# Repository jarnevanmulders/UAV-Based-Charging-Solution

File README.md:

# UAV Based Charging Solution

- [NRF52832 DK pinout](https://os.mbed.com/platforms/Nordic-nRF52-DK/)
- [NRF52832 DK schematics](https://devzone.nordicsemi.com/cfs-file/__key/communityserver-discussions-components-files/4/PCA10040_5F00_Schematic_5F00_And_5F00_PCB.pdf)

# HW design
- [BLE 2.4GHz antenna design](https://www.infineon.com/dgdl/Infineon-AN91445_Antenna_Design_and_RF_Layout_Guidelines-ApplicationNotes-v09_00-EN.pdf)

# Image hardware

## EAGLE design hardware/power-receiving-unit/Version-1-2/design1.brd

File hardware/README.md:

# Hardware status
## PRU
Working

Updates from v1.0 to v1.1
- I2C programmable load
- VDD_BLE directly connected to ADC pin P03 (without voltage divider)
- Additional RC filter after current limiter OPAMP
- Button from pull-up to pull down
- Additional filter (ferrite bead) on VDD_BLE supply line
- Other load switch implementation (with dual PMOS PMDPB55XP)
- Diode and shunt resistor location changed
- MIFA antenna tuning
  - Measured impedance 25+j25
    - Measured with R&S ZVL 3GHz VNA
    - Used a calibrated UFL connector cable (calibrated with ZVL one port calibration procedure)
    - Blank PCB board was used for measurement
  - Added 1.2 pF parallel with antenna (as compensation (see Smith V4.1))
  - Total [Pi] matching circuit (MCU - 0.8 pF capacitor - 3.9 nH inductor - 1.2 pF capacitor)

## PTU

### Architecture

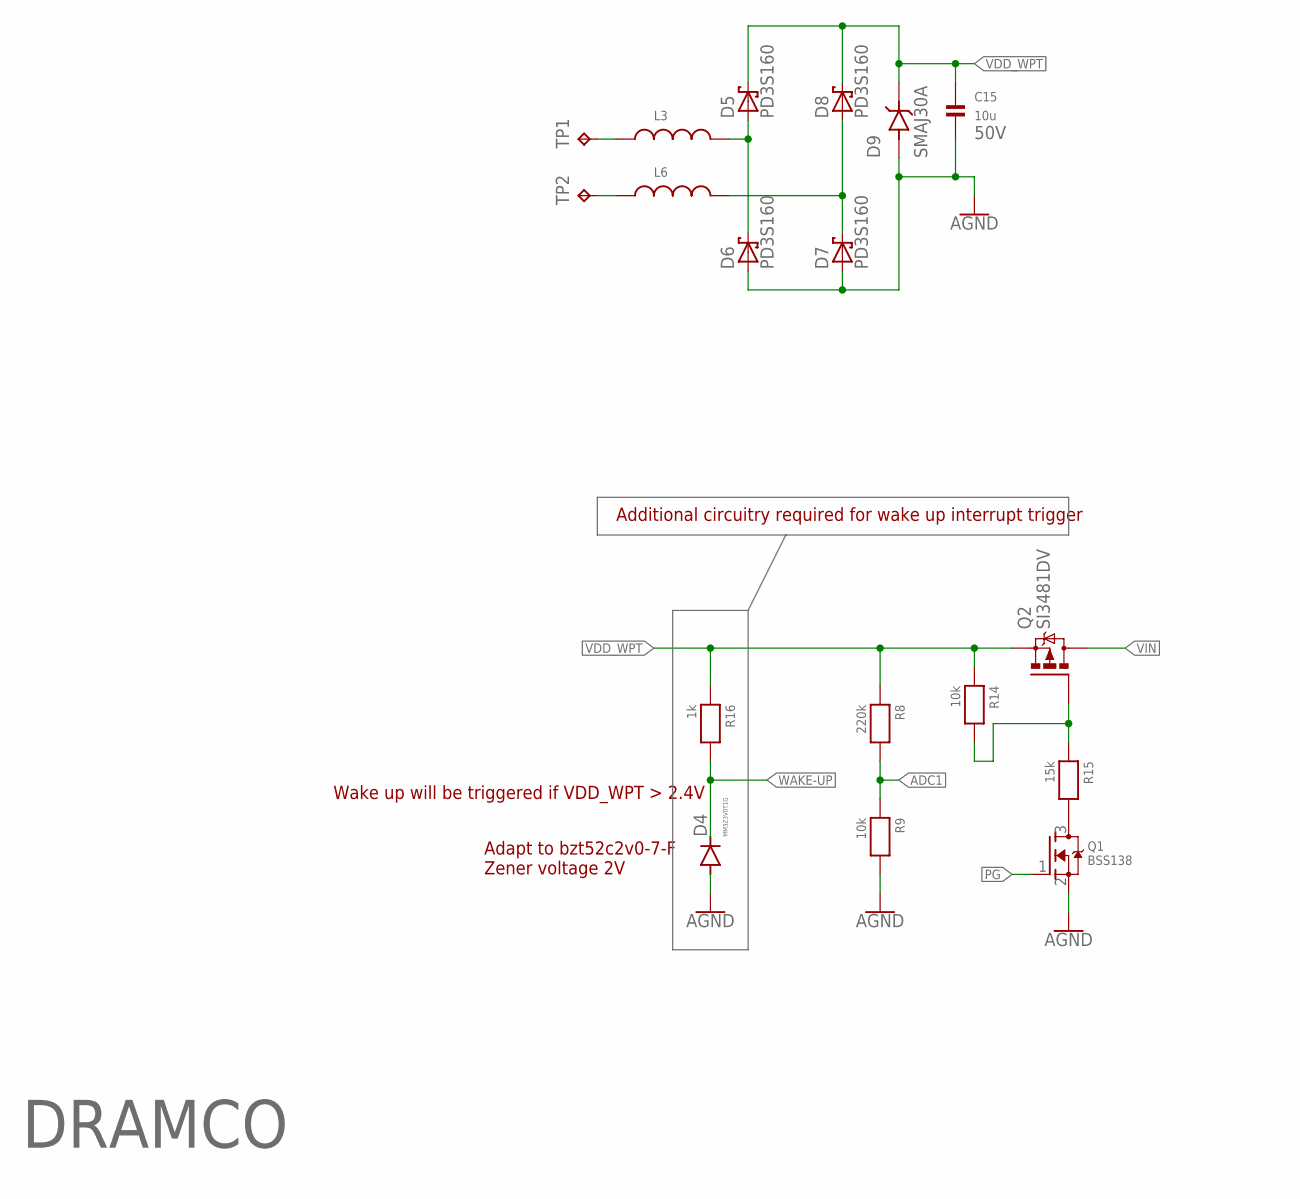
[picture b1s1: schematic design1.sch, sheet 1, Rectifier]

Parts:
C15: 10u; 1206
D4: MM3Z3V0T1G; SOD323-R
D5, D6, D7, D8: PD3S160; POWERDI323
D9: SMAJ30A; DIOM5026X229N
L3, L6: WE-CAIR_4248_744912182; WE-CAIR_4248
Q1: BSS138; SOT23-R
Q2: SI3481DV; TSOP-6.PAC
R8: 220k; 0603
R9, R14: 10k; 0603
R15: 15k; 0603
R16: 1k; 0603
TP1, TP2: TPTP20SQ; TP20SQ

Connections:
ADC1: R8.2, R9.1; also elsewhere on the board
AGND: C15.2, D4.A, D6.A, D7.A, D9.A, Q1.2 (S), R9.2; also elsewhere on the board
unnamed: Q1.3 (D), R15.2
unnamed: Q2.3 (G), R14.2, R15.1
unnamed: L6.1, TP2.TP
unnamed: L3.1, TP1.TP
unnamed: D5.A, D6.C, L3.2
unnamed: D7.C, D8.A, L6.2
PG: Q1.1 (G); also elsewhere on the board
VDD_WPT: C15.1, D5.C, D8.C, D9.C, Q2.4 (S), R8.1, R14.1, R16.1
VIN: Q2.1 (D), Q2.2 (D), Q2.5 (D), Q2.6 (D); also elsewhere on the board
WAKE-UP: D4.C, R16.2; also elsewhere on the board

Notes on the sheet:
Additional circuitry required for wake up interrupt trigger
50V
DRAMCO
Adapt to bzt52c2v0-7-F Zener voltage 2V
Wake up will be triggered if VDD_WPT > 2.4V

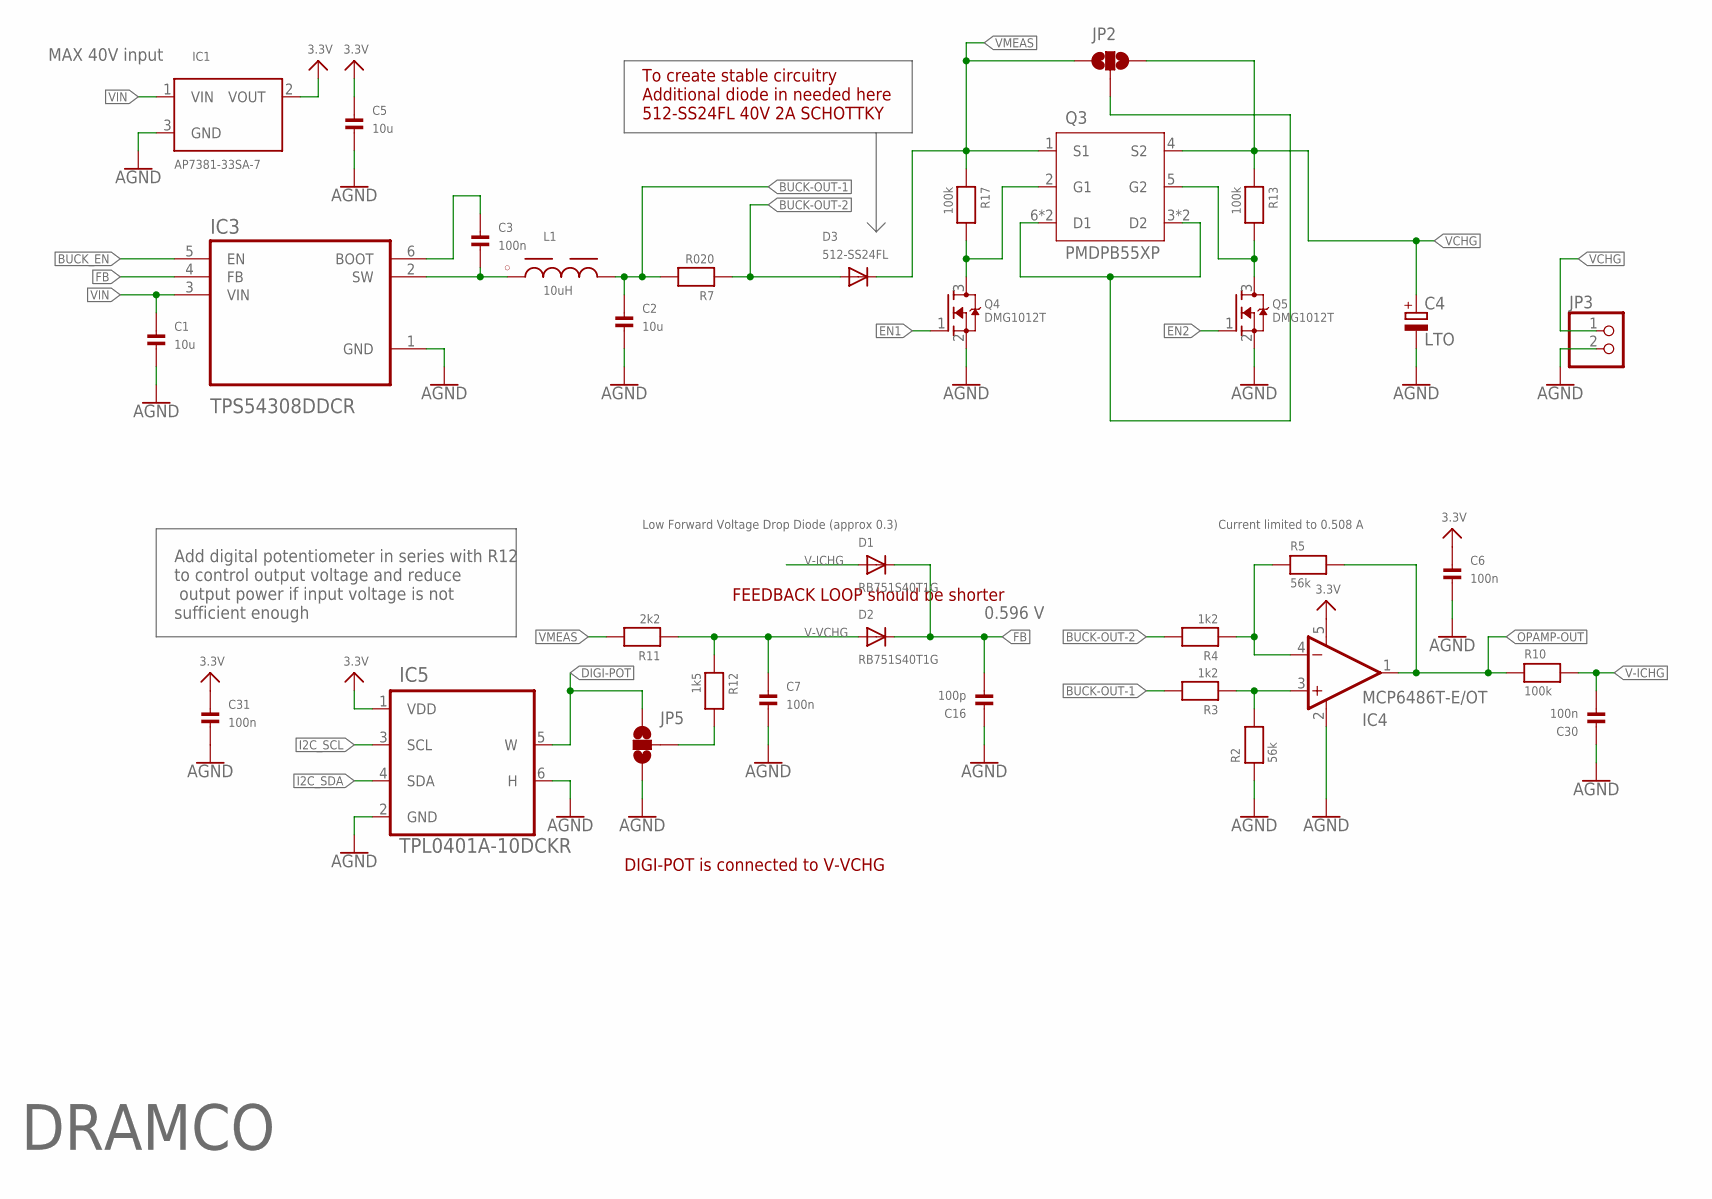
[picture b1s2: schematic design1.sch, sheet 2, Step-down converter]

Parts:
C1, C2, C5: 10u; 0603
C3, C7, C30: 100n; 0603
C4: LTO; E5-10,5
C6, C31: 100n; 0402
C16: 100p; 0603
D1, D2: RB751S40T1G; SOD-523
D3: 512-SS24FL; SOD-123
IC1: AP7381-33SA-7; SOT23-R
IC3: TPS54308DDCR; SOT95P280X110-6N
IC4: MCP6486T-E/OT; SOT23-5
IC5: TPL0401A-10DCKR; SOT65P210X110-6N
JP2, JP5: JUMPER-SMT_3_NO_NO-SILK; SMT-JUMPER_3_NO_NO-SILK
JP3: HEADER-1X2ROUND; 1X02_ROUND
L1: 10uH; WE-PD_7332/7345_PLASTIC_BASE
Q3: PMDPB55XP; SON65P200X200X65-8N
Q4, Q5: DMG1012T; SOT523-3
R2, R5: 56k; 0603
R3, R4: 1k2; 0603
R7: R020; 0603
R10: 100k; 0603
R11: 2k2; 0603
R12: 1k5; 0603
R13, R17: 100k; 0402

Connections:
3.3V: C5.1, C6.1, C31.1, IC1.2 (VOUT), IC4.5 (V+), IC5.1 (VDD)
AGND: C1.2, C2.2, C4.-, C5.2, C6.2, C7.2, C16.1, C30.1, C31.2, IC1.3 (GND), IC3.1 (GND), IC4.2 (V-), IC5.2 (GND), IC5.6 (H), JP3.2, JP5.1, Q4.2 (S), Q5.2 (S), R2.1; also elsewhere on the board
BUCK-OUT-1: C2.1, L1.2, R3.2, R7.2
BUCK-OUT-2: D3.A, R4.2, R7.1
BUCK_EN: IC3.5 (EN); also elsewhere on the board
DIGI-POT: IC5.5 (W), JP5.3
EN1: Q4.1 (G); also elsewhere on the board
EN2: Q5.1 (G); also elsewhere on the board
FB: C16.2, D1.K (C), D2.K (C), IC3.4 (FB)
I2C_SCL: IC5.3 (SCL); also elsewhere on the board
I2C_SDA: IC5.4 (SDA); also elsewhere on the board
unnamed: JP2.2, Q3.3 (D2), Q3.6 (D1), Q3.7 (D1), Q3.8 (D2)
unnamed: C3.1, IC3.6 (BOOT)
unnamed: C3.2, IC3.2 (SW), L1.1
unnamed: JP5.2, R12.2
unnamed: IC4.4 (-IN), R4.1, R5.1
unnamed: IC4.3 (+IN), R2.2, R3.1
unnamed: Q3.2 (G1), Q4.3 (D), R17.2
unnamed: Q3.5 (G2), Q5.3 (D), R13.2
OPAMP-OUT: IC4.1 (OUT), R5.2, R10.1
V-ICHG: C30.2, D1.A, R10.2; also elsewhere on the board
V-VCHG: C7.1, D2.A, R11.1, R12.1
VCHG: C4.+, JP2.3, JP3.1, Q3.4 (S2), R13.1; also elsewhere on the board
VIN: C1.1, IC1.1 (VIN), IC3.3 (VIN); also elsewhere on the board
VMEAS: D3.C, JP2.1, Q3.1 (S1), R11.2, R17.1

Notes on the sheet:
Low Forward Voltage Drop Diode (approx 0.3)
0.596 V
To create stable circuitry Additional diode in needed here 512-SS24FL 40V 2A SCHOTTKY
Add digital potentiometer in series with R12 to control output voltage and reduce output power if input voltage is not sufficient enough
DRAMCO
Current limited to 0.508 A
MAX 40V input
DIGI-POT is connected to V-VCHG
FEEDBACK LOOP should be shorter

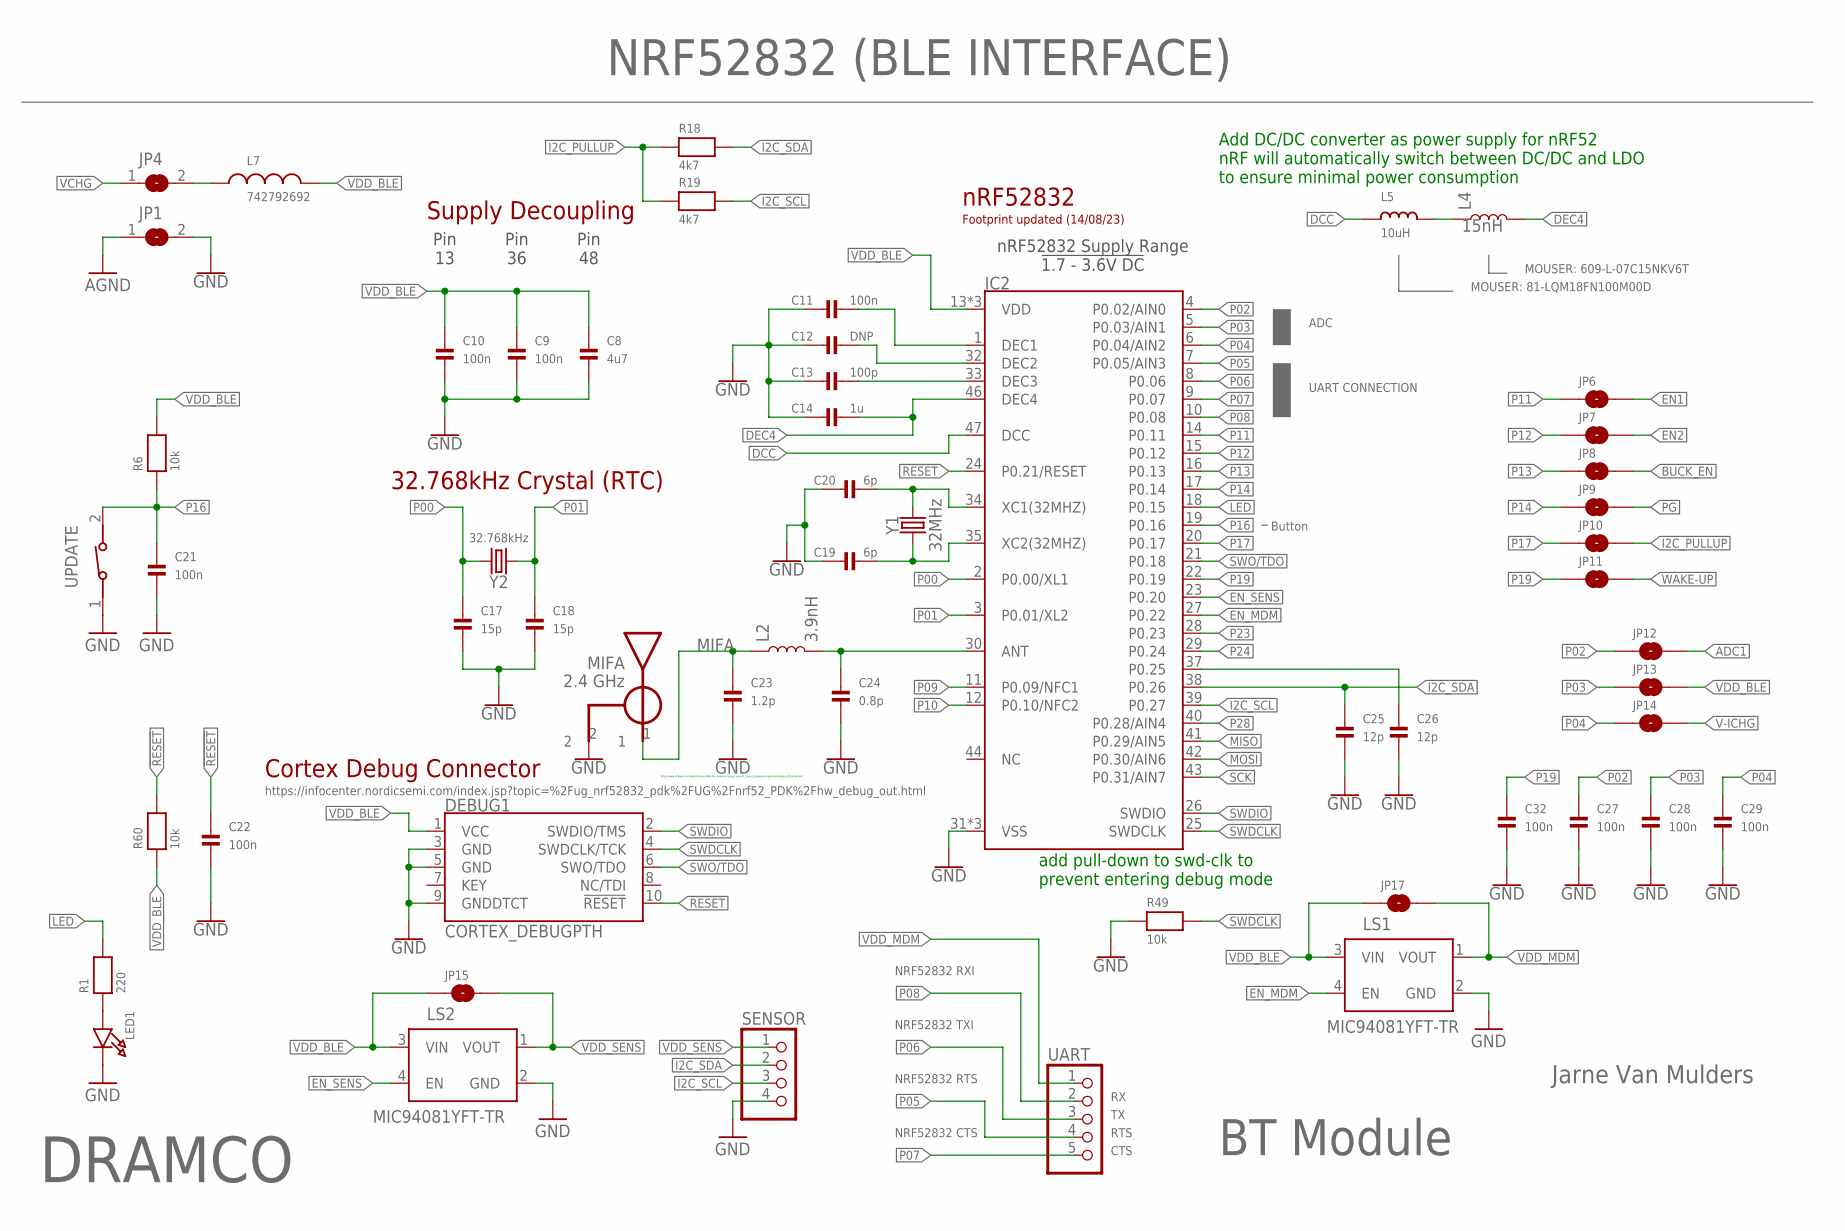
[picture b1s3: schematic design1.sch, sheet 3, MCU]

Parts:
C8: 4u7; 0603
C9, C10, C11, C21, C22, C27, C28, C29, C32: 100n; 0402
C12: DNP; 0402
C13: 100p; 0402
C14: 1u; 0402
C17, C18: 15p; 0402
C19, C20: 6p; 0402
C23: 1.2p; 0402
C24: 0.8p; 0402
C25, C26: 12p; 0402
DEBUG1: CORTEX_DEBUGPTH; 2X5-PTH-1.27MM
IC2: NRF52832-EXTENDED; QFN48-6X6MM-EXTENDED
JP1, JP4: SOLDERJUMPERREFLOW_NOPASTE; SOLDERJUMPER_REFLOW_NOPASTE
JP6, JP7, JP8, JP9, JP10, JP11, JP12, JP13, JP14, JP15, JP17: JUMPER-SMT_2_NO_NO-SILK; SMT-JUMPER_2_NO_NO-SILK
L2: 3.9nH; 0402
L4: 15nH; 0402
L5: 10uH; _0603MP
L7: 742792692; WE-CBF_0603(W=2.2)
LED1: LED0805; CHIPLED_0805
LS1, LS2: MIC94081YFT-TR; IC_MIC94081YFT-TR
R1: 220; 0603
R6, R49, R60: 10k; 0402
R18, R19: 4k7; 0402
SENSOR: HEADER-1X4ROUND; 1X04_ROUND
U$18: BLE-ANT; ANT-2G4
UART: HEADER-1X5ROUND; 1X05_ROUND
UPDATE: 434111043826
Y1: 32MHz; CRYSTAL-SMD-2.0X1.6MM
Y2: 32.768kHz; CRYSTAL-SMD-3.2X1.5MM

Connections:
!RESET!: C22.1, DEBUG1.10 (!RESET), IC2.24 (P0.21/RESET), R60.2
ADC1: JP12.2; also elsewhere on the board
AGND: JP1.1; also elsewhere on the board
ANT: C24.1, IC2.30 (ANT), L2.2
BUCK_EN: JP8.2; also elsewhere on the board
DCC: IC2.47 (DCC), L5.1
DEC4: C14.2, IC2.46 (DEC4), L4.2
DEC5: C11.2, IC2.1 (DEC1)
DEC6: C12.2, IC2.32 (DEC2)
DEC8: C13.2, IC2.33 (DEC3)
EN1: JP6.2; also elsewhere on the board
EN2: JP7.2; also elsewhere on the board
EN_MDM: IC2.27 (P0.22), LS1.4 (EN)
EN_SENS: IC2.23 (P0.20), LS2.4 (EN)
GND: C8.2, C9.2, C10.2, C11.1, C12.1, C13.1, C14.1, C17.2, C18.2, C19.1, C20.1, C21.2, C22.2, C23.2, C24.2, C25.2, C26.2, C27.2, C28.2, C29.2, C32.2, DEBUG1.3 (GND), DEBUG1.5 (GND), DEBUG1.9 (GNDDTCT), IC2.31 (VSS), IC2.45 (VSS), IC2.EP (VSS), JP1.2, LED1.C, LS1.2 (GND), LS2.2 (GND), R49.1, SENSOR.4, U$18.2, UPDATE.1
I2C_PULLUP: JP10.2, R18.1, R19.1
I2C_SCL: IC2.39 (P0.27), R19.2, SENSOR.3; also elsewhere on the board
I2C_SDA: C25.1, IC2.38 (P0.26), R18.2, SENSOR.2; also elsewhere on the board
LED: IC2.18 (P0.15), R1.2
MIFA: C23.1, L2.1, U$18.1
MISO: IC2.41 (P0.29/AIN5)
MOSI: IC2.42 (P0.30/AIN6)
unnamed: JP4.2, L7.1
unnamed: LED1.A, R1.1
unnamed: C26.1, IC2.37 (P0.25)
unnamed: L4.1, L5.2
P00: C17.1, IC2.2 (P0.00/XL1), Y2.P$2 (2)
P01: C18.1, IC2.3 (P0.01/XL2), Y2.P$1 (1)
P02: C27.1, IC2.4 (P0.02/AIN0), JP12.1
P03: C28.1, IC2.5 (P0.03/AIN1), JP13.1
P04: C29.1, IC2.6 (P0.04/AIN2), JP14.1
P05: IC2.7 (P0.05/AIN3), UART.4
P06: IC2.8 (P0.06), UART.3
P07: IC2.9 (P0.07), UART.5
P08: IC2.10 (P0.08), UART.2
P09: IC2.11 (P0.09/NFC1)
P10: IC2.12 (P0.10/NFC2)
P11: IC2.14 (P0.11), JP6.1
P12: IC2.15 (P0.12), JP7.1
P13: IC2.16 (P0.13), JP8.1
P14: IC2.17 (P0.14), JP9.1
P16: C21.1, IC2.19 (P0.16), R6.1, UPDATE.2
P17: IC2.20 (P0.17), JP10.1
P19: C32.1, IC2.22 (P0.19), JP11.1
P23: IC2.28 (P0.23)
P24: IC2.29 (P0.24)
P28: IC2.40 (P0.28/AIN4)
PG: JP9.2; also elsewhere on the board
SCK: IC2.43 (P0.31/AIN7)
SWDCLK: DEBUG1.4 (SWDCLK/TCK), IC2.25 (SWDCLK), R49.2
SWDIO: DEBUG1.2 (SWDIO/TMS), IC2.26 (SWDIO)
SWO/TDO: DEBUG1.6 (SWO/TDO), IC2.21 (P0.18)
V-ICHG: JP14.2; also elsewhere on the board
VCHG: JP4.1; also elsewhere on the board
VDD_BLE: C8.1, C9.1, C10.1, DEBUG1.1 (VCC), IC2.13 (VDD), IC2.36 (VDD), IC2.48 (VDD), JP13.2, JP15.1, JP17.1, L7.2, LS1.3 (VIN), LS2.3 (VIN), R6.2, R60.1
VDD_MDM: JP17.2, LS1.1 (VOUT), UART.1
VDD_SENS: JP15.2, LS2.1 (VOUT), SENSOR.1
WAKE-UP: JP11.2; also elsewhere on the board
XC1: C20.2, IC2.34 (XC1(32MHZ)), Y1.3 (2)
XC2: C19.2, IC2.35 (XC2(32MHZ)), Y1.1

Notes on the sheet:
BT Module
Jarne Van Mulders
DRAMCO
NRF52832 (BLE INTERFACE)
Pin 13
Pin 36
Pin 48
nRF52832
32.768kHz Crystal (RTC)
Supply Decoupling
Cortex Debug Connector
nRF52832 Supply Range !1.7 - 3.6V DC!
Add DC/DC converter as power supply for nRF52 nRF will automatically switch between DC/DC and LDO to ensure minimal power consumption
add pull-down to swd-clk to prevent entering debug mode
NRF52832 RXI
NRF52832 TXI
NRF52832 RTS
NRF52832 CTS
MOUSER: 81-LQM18FN100M00D
MOUSER: 609-L-07C15NKV6T
RTS
CTS
UART CONNECTION
Button
ADC
https://www.infineon.com/dgdl/Infineon-AN91445_Antenna_Design_and_RF_Layout_Guidelines-ApplicationNotes-v09_00-EN.pdf
https://infocenter.nordicsemi.com/index.jsp?topic=%2Fug_nrf52832_pdk%2FUG%2Fnrf52_PDK%2Fhw_debug_out.html
Footprint updated (14/08/23)

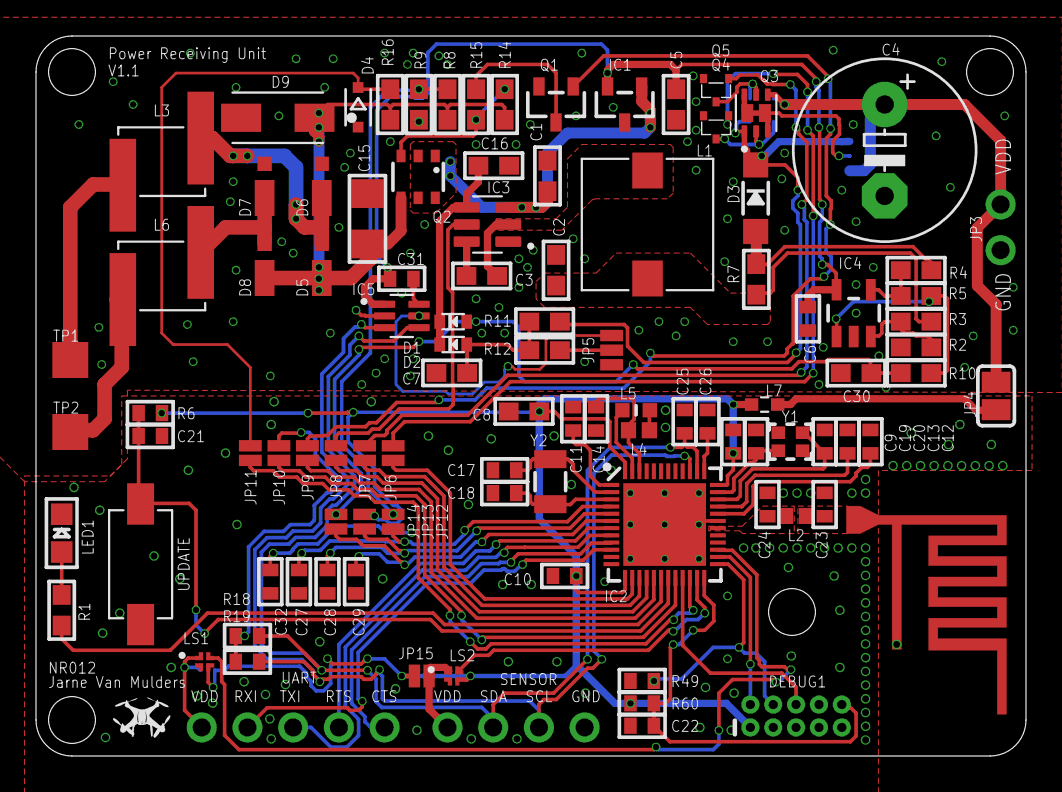
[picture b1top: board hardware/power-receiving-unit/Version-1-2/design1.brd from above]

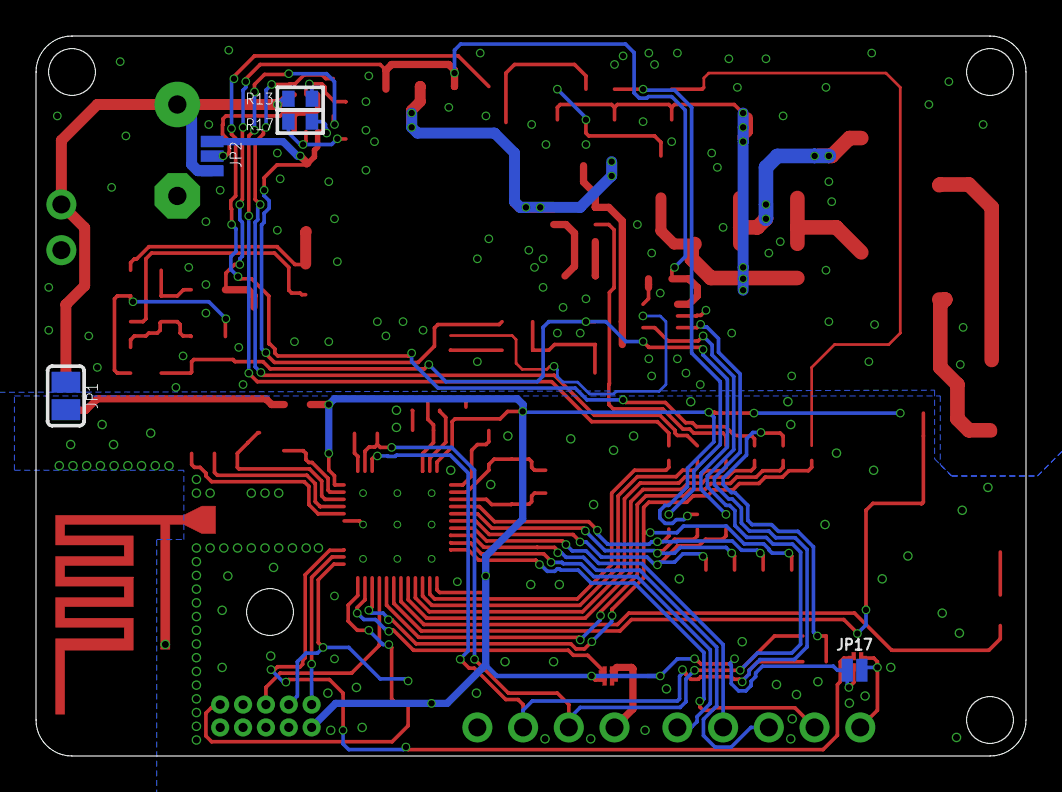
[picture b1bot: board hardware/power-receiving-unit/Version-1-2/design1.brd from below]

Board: 2 copper layers, 55.0 x 40.0 mm, 107 parts (5 on the bottom side), 76 nets.

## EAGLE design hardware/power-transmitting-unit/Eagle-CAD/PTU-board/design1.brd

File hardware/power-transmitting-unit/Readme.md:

## Hardware status

## Architecture

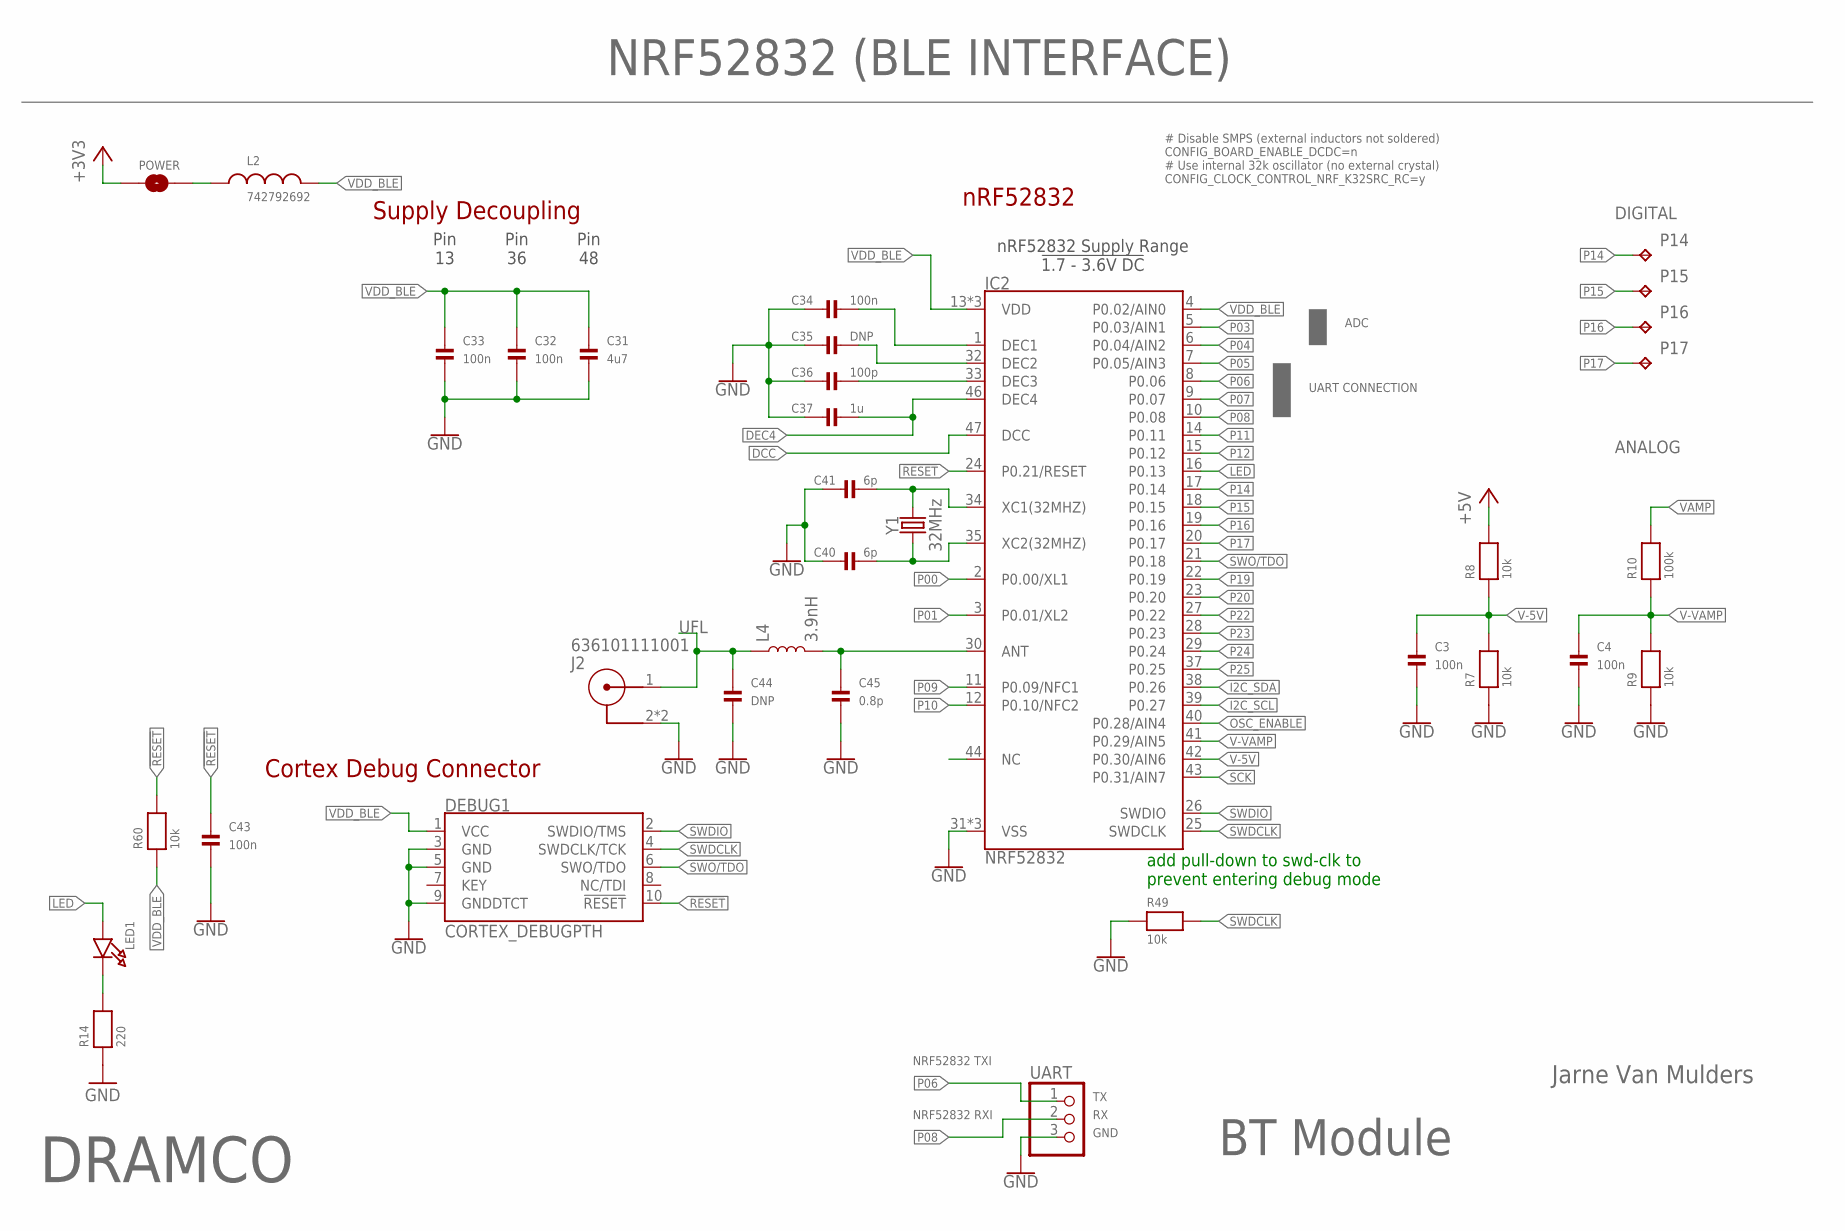
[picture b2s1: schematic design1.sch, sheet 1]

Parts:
C3, C4, C32, C33, C34, C43: 100n; 0402
C31: 4u7; 0603
C35, C44: DNP; 0402
C36: 100p; 0402
C37: 1u; 0402
C40, C41: 6p; 0402
C45: 0.8p; 0402
DEBUG1: CORTEX_DEBUGPTH; 2X5-PTH-1.27MM
IC2: NRF52832; QFN48-6X6MM-EXTENDED
J2: 636101111001
L2: 742792692; WE-CBF_0603(W=2.2)
L4: 3.9nH; 0402
LED1: LED0805; CHIPLED_0805
P14, P15, P16, P17: TPTP10SQ; TP10SQ
POWER: JUMPER-SMT_2_NO_NO-SILK; SMT-JUMPER_2_NO_NO-SILK
R7, R8, R9, R49, R60: 10k; 0402
R10: 100k; 0402
R14: 220; 0603
UART: HEADER-1X3ROUND; 1X03_ROUND
Y1: 32MHz; CRYSTAL-SMD-2.0X1.6MM

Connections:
!RESET!: C43.1, DEBUG1.10 (!RESET), IC2.24 (P0.21/RESET), R60.2
+3V3: POWER.1; also elsewhere on the board
+5V: R8.2; also elsewhere on the board
ANT: C45.1, IC2.30 (ANT), L4.2
DCC: IC2.47 (DCC)
DEC4: C37.2, IC2.46 (DEC4)
DEC5: C34.2, IC2.1 (DEC1)
DEC6: C35.2, IC2.32 (DEC2)
DEC8: C36.2, IC2.33 (DEC3)
GND: C3.2, C4.2, C31.2, C32.2, C33.2, C34.1, C35.1, C36.1, C37.1, C40.1, C41.1, C43.2, C44.2, C45.2, DEBUG1.3 (GND), DEBUG1.5 (GND), DEBUG1.9 (GNDDTCT), IC2.31 (VSS), IC2.45 (VSS), IC2.EP (VSS), J2.2, J2.3 (2), R7.1, R9.1, R14.1, R49.1, UART.3; also elsewhere on the board
I2C_SCL: IC2.39 (P0.27); also elsewhere on the board
I2C_SDA: IC2.38 (P0.26); also elsewhere on the board
LED: IC2.16 (P0.13), LED1.A
unnamed: LED1.C, R14.2
unnamed: L2.1, POWER.2
NC: IC2.44 (NC)
OSC_ENABLE: IC2.40 (P0.28/AIN4); also elsewhere on the board
P00: IC2.2 (P0.00/XL1)
P01: IC2.3 (P0.01/XL2)
P03: IC2.5 (P0.03/AIN1)
P04: IC2.6 (P0.04/AIN2)
P05: IC2.7 (P0.05/AIN3)
P06: IC2.8 (P0.06), UART.1
P07: IC2.9 (P0.07)
P08: IC2.10 (P0.08), UART.2
P09: IC2.11 (P0.09/NFC1)
P10: IC2.12 (P0.10/NFC2)
P11: IC2.14 (P0.11)
P12: IC2.15 (P0.12)
P14: IC2.17 (P0.14), P14.TP
P15: IC2.18 (P0.15), P15.TP
P16: IC2.19 (P0.16), P16.TP
P17: IC2.20 (P0.17), P17.TP
P19: IC2.22 (P0.19)
P20: IC2.23 (P0.20)
P22: IC2.27 (P0.22)
P23: IC2.28 (P0.23)
P24: IC2.29 (P0.24)
P25: IC2.37 (P0.25)
SCK: IC2.43 (P0.31/AIN7)
SWDCLK: DEBUG1.4 (SWDCLK/TCK), IC2.25 (SWDCLK), R49.2
SWDIO: DEBUG1.2 (SWDIO/TMS), IC2.26 (SWDIO)
SWO/TDO: DEBUG1.6 (SWO/TDO), IC2.21 (P0.18)
UFL: C44.1, J2.1, L4.1
V-5V: C3.1, IC2.42 (P0.30/AIN6), R7.2, R8.1
V-VAMP: C4.1, IC2.41 (P0.29/AIN5), R9.2, R10.1
VAMP: R10.2; also elsewhere on the board
VDD_BLE: C31.1, C32.1, C33.1, DEBUG1.1 (VCC), IC2.4 (P0.02/AIN0), IC2.13 (VDD), IC2.36 (VDD), IC2.48 (VDD), L2.2, R60.1
XC1: C41.2, IC2.34 (XC1(32MHZ)), Y1.3 (2)
XC2: C40.2, IC2.35 (XC2(32MHZ)), Y1.1

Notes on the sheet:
BT Module
Jarne Van Mulders
DRAMCO
NRF52832 (BLE INTERFACE)
Pin 13
Pin 36
Pin 48
nRF52832
Supply Decoupling
Cortex Debug Connector
nRF52832 Supply Range !1.7 - 3.6V DC!
add pull-down to swd-clk to prevent entering debug mode
NRF52832 RXI
NRF52832 TXI
UART CONNECTION
ADC
ANALOG
DIGITAL
# Disable SMPS (external inductors not soldered) CONFIG_BOARD_ENABLE_DCDC=n # Use internal 32k oscillator (no external crystal) CONFIG_CLOCK_CONTROL_NRF_K32SRC_RC=y
GND

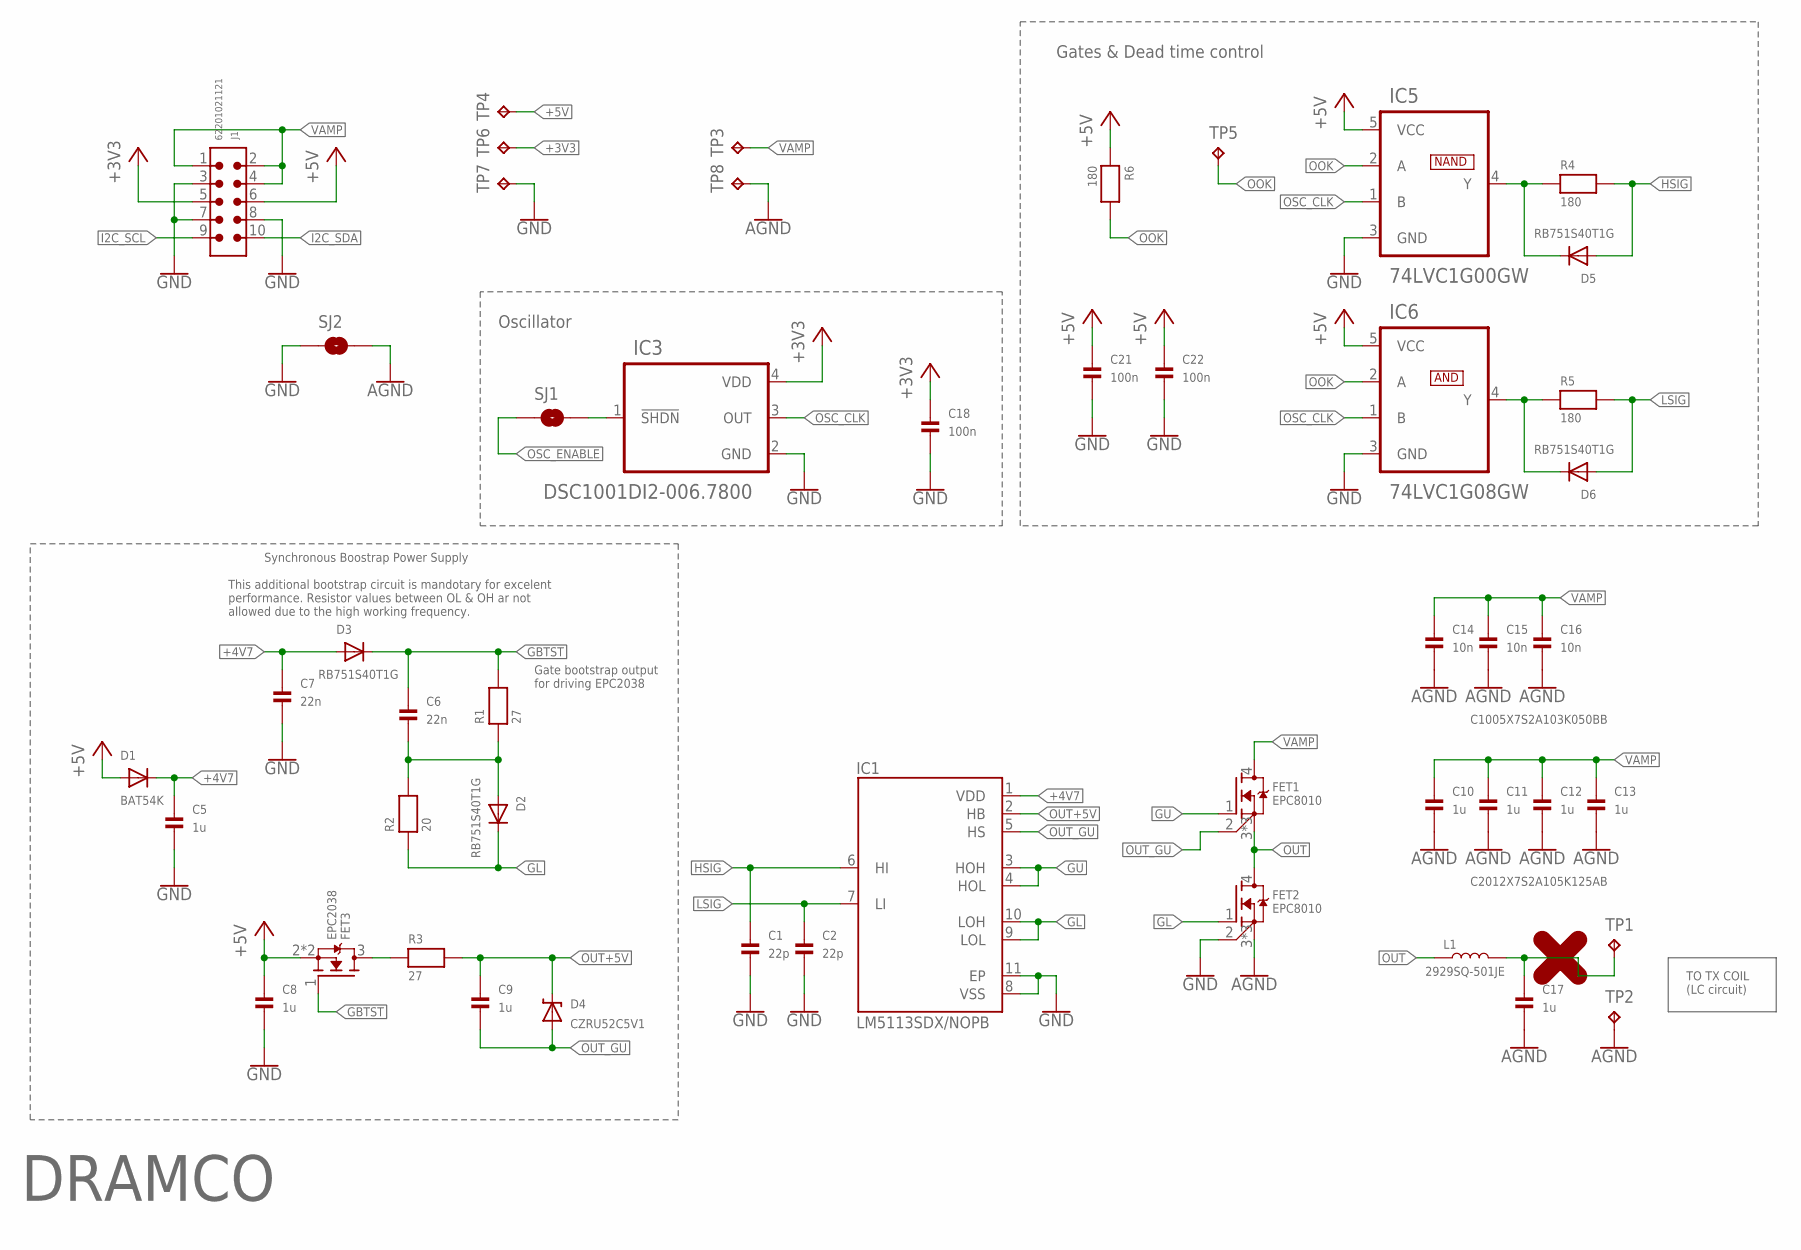
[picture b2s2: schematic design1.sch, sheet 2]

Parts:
C1, C2: 22p; 0402
C5, C8, C9: 1u; 0402
C6, C7: 22n; 0402
C10, C11, C12, C13, C17: 1u; 0805
C14, C15, C16: 10n; 0402
C18: 100n; 0603
C21, C22: 100n; 0402
D1: BAT54K; SOD-523
D2, D3, D5, D6: RB751S40T1G; SOD-523
D4: CZRU52C5V1; SOD-523F
FET1, FET2: EPC8010; BGA-8010
FET3: EPC2038; BGA-2038
IC1: LM5113SDX/NOPB; SON80P400X400X80-11N
IC3: DSC1001DI2-006.7800; 2.5X2.0MMPLASTICPACKAGE
IC5: 74LVC1G00GW; SOT65P210X110-5N
IC6: 74LVC1G08GW; SOT65P210X110-5N
J1: 62201021121
L1: 2929SQ-501JE; 2929SQ-501
R1, R3: 27; 0402
R2: 20; 0402
R4, R5, R6: 180; 0402
SJ1, SJ2: SOLDERJUMPERNO; SJ_2S-NO
TP1, TP2, TP3, TP8: TPTP20SQ; TP20SQ
TP4, TP5, TP6, TP7: TPTP10SQ; TP10SQ

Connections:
+3V3: C18.1, IC3.4 (VDD), J1.5, TP6.TP; also elsewhere on the board
+4V7: C5.1, C7.1, D1.K (C), D3.A, IC1.1 (VDD)
+5V: C8.1, C21.1, C22.1, D1.A, FET3.2 (S), FET3.4 (S), IC5.5 (VCC), IC6.5 (VCC), J1.6, R6.1, TP4.TP; also elsewhere on the board
AGND: C10.2, C11.2, C12.2, C13.2, C14.2, C15.2, C16.2, C17.2, FET2.3 (S), FET2.5 (S), FET2.6 (S), SJ2.2, TP2.TP, TP8.TP
GBTST: C6.1, D3.K (C), FET3.1 (G), R1.2
GL: D2.K (C), FET2.1 (G), IC1.9 (LOL), IC1.10 (LOH), R2.1
GND: C1.2, C2.2, C5.2, C7.2, C8.2, C18.2, C21.2, C22.2, FET2.2 (SR), IC1.8 (VSS), IC1.11 (EP), IC3.2 (GND), IC5.3 (GND), IC6.3 (GND), J1.3, J1.7, J1.8, SJ2.1, TP7.TP; also elsewhere on the board
GU: FET1.1 (G), IC1.3 (HOH), IC1.4 (HOL)
HSIG: C1.1, D5.A, IC1.6 (HI), R4.2
I2C_SCL: J1.9; also elsewhere on the board
I2C_SDA: J1.10; also elsewhere on the board
LSIG: C2.1, D6.A, IC1.7 (LI), R5.2
unnamed: FET3.3 (D), R3.1
unnamed: D5.K (C), IC5.4 (Y), R4.1
unnamed: IC3.1 (!SHDN!), SJ1.2
unnamed: D6.K (C), IC6.4 (Y), R5.1
unnamed: C6.2, D2.A, R1.1, R2.2
unnamed: C17.1, L1.2, TP1.TP
OOK: IC5.2 (A), IC6.2 (A), R6.2, TP5.TP
OSC_CLK: IC3.3 (OUT), IC5.1 (B), IC6.1 (B)
OSC_ENABLE: SJ1.1; also elsewhere on the board
OUT: FET1.3 (S), FET1.5 (S), FET1.6 (S), FET2.4 (D), L1.1
OUT+5V: C9.1, D4.1 (C), IC1.2 (HB), R3.2
OUT_GU: C9.2, D4.2 (A), FET1.2 (SR), IC1.5 (HS)
VAMP: C10.1, C11.1, C12.1, C13.1, C14.1, C15.1, C16.1, FET1.4 (D), J1.1, J1.2, J1.4, TP3.TP; also elsewhere on the board

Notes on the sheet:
Synchronous Boostrap Power Supply
This additional bootstrap circuit is mandotary for excelent performance. Resistor values between OL & OH ar not allowed due to the high working frequency.
Gate bootstrap output for driving EPC2038
C2012X7S2A105K125AB
C1005X7S2A103K050BB
TO TX COIL (LC circuit)
NAND
AND
Gates & Dead time control
Oscillator
DRAMCO

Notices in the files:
parts and their libraries:
microbuilder: This work is placed in the public domain, and may be freely used for commercial and non-commercial work with the following conditions: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
EMCComponents: Copyright: Würth Elektronik
